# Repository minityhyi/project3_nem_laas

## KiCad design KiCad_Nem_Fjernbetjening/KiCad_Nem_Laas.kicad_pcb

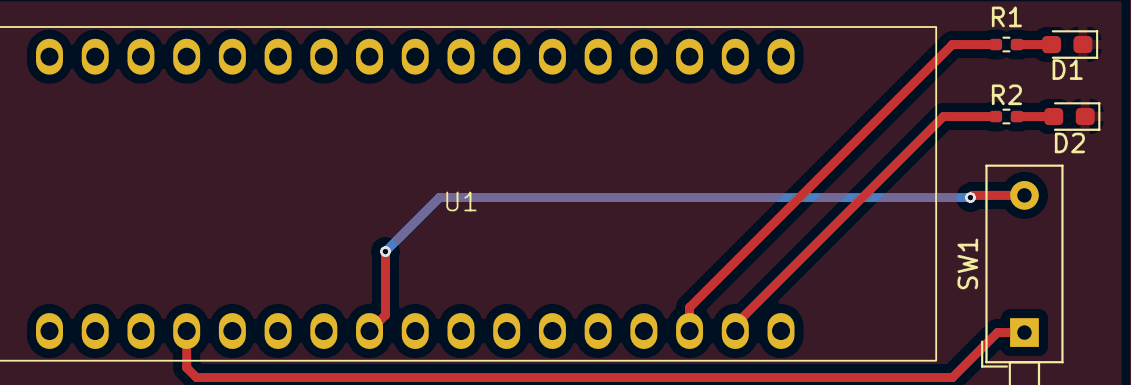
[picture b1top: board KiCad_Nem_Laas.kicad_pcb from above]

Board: 2 copper layers, 6 parts (0 on the bottom side), 7 nets.

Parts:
D1, D2: LED; LED_0603_1608Metric_Pad1.05x0.95mm_HandSolder
R1, R2: 220; R_0402_1005Metric_Pad0.72x0.64mm_HandSolder
SW1: SW_Push; SW_DIP_SPSTx01_Piano_10.8x4.1mm_W7.62mm_P2.54mm
U1: ProS3; ESP32-PROS3

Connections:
GND: D1.1 (K), D2.1 (K)
unnamed: D1.2 (A), R1.2
unnamed: D2.2 (A), R2.2
unnamed: SW1.1, U1.4 (3V3)
unnamed: SW1.2, U1.8 (IO4)
unnamed: R2.1, U1.16 (IO13)
unnamed: R1.1, U1.15 (IO14)

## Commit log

2024-09-18 start Kicad
2024-09-18 Færdig schematic og pcb
2024-09-24 lockSchematic
2024-10-08 ble prototype
2024-10-11 Opdatering til motorkontrol
    Fjernbetjening kan nu kontrollere motor
2024-10-16 Handshake, basic
    Adgang gives baseret på MAC adresse
2024-10-16 Opdatering med CSV logging
    Nu logges opdateringerne i en CSV fil.
2024-10-17 Wifi og flaskeserver til lagring af CSV
2024-10-17 Rettelser
2024-10-18 Upload CSV fra NemLås til server
2024-10-18 Update med setup config på BLE server
    BLEClient genforbinder sig automatisk hvis forbindelsen til BLEserver stopper.
    BLEserver spørger nu om Wifi info etc. indenfor 5 sekunder fra opstart.
2024-10-24 asdaw
2024-10-28 hejsa
2024-10-28 Sammenbygning af de to API scripts
2024-11-07 Door UUID
2024-11-07 push button
2024-11-21 Lock state update - lortet virker faktisk
2024-11-25 det virker
2024-11-27 Update lortet virker
2024-12-02 Scheduling update
